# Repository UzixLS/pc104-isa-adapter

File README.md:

## PC104-ISA-ADAPTER
PC104 to ISA 16 bit adapter

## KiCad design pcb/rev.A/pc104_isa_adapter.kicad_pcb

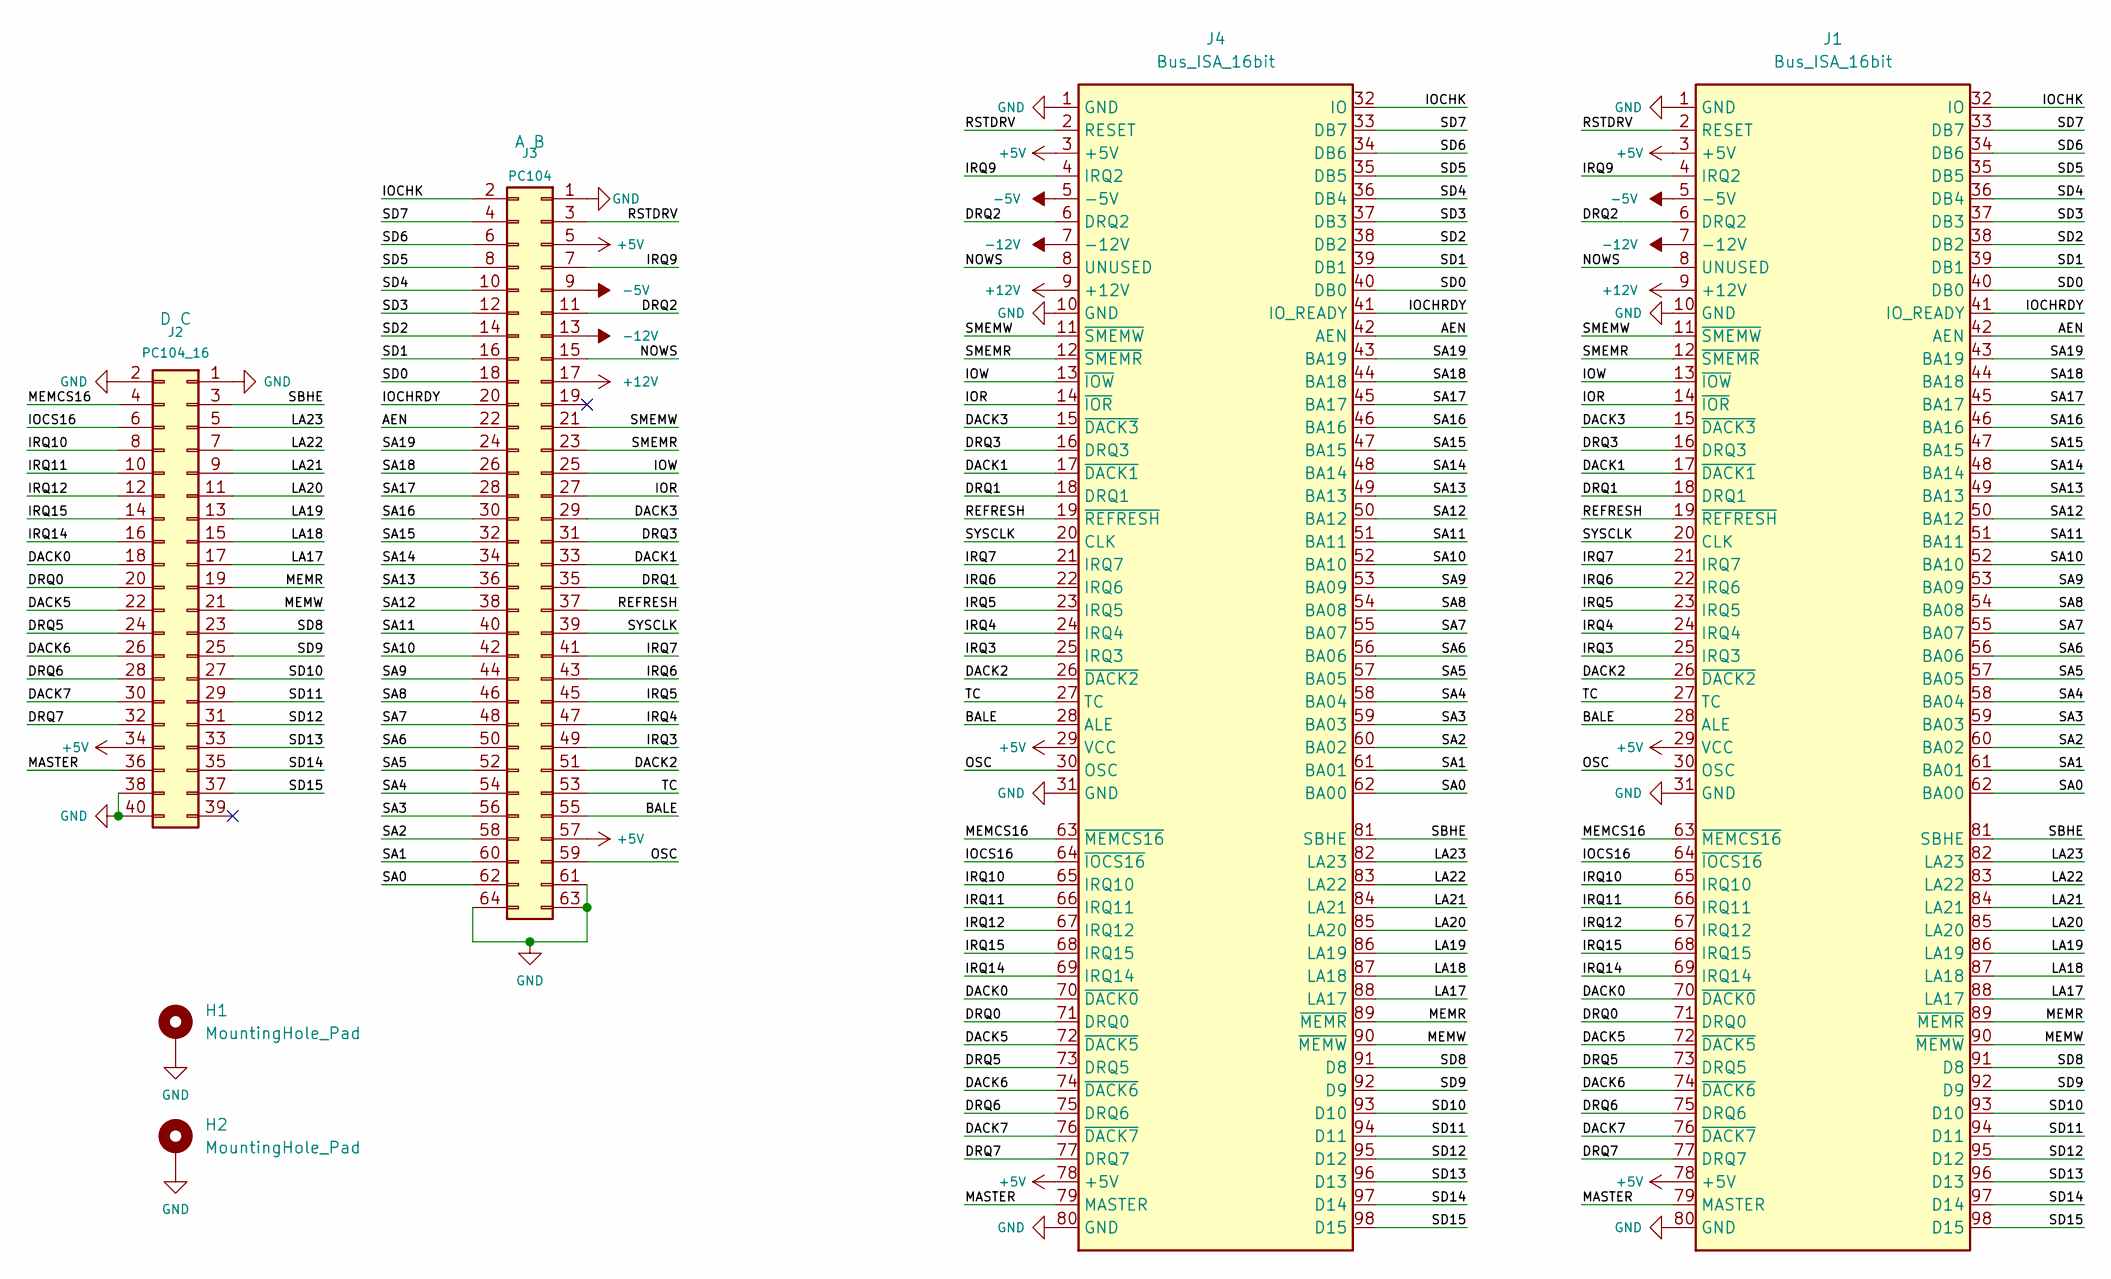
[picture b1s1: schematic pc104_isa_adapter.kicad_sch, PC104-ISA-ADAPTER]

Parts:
H1, H2: MountingHole_Pad; MountingHole_3.2mm_M3_Pad
J1: Bus_ISA_16bit; ISA16_EDGE
J2: PC104_16; PinSocket_2x20_P2.54mm_Vertical
J3: PC104; PinSocket_2x32_P2.54mm_Vertical
J4: Bus_ISA_16bit; ISA16

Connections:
+5V: J1.3 (+5V), J1.29 (VCC), J1.78 (+5V), J2.34, J3.5, J3.57, J4.3 (+5V), J4.29 (VCC), J4.78 (+5V)
+12V: J1.9 (+12V), J3.17, J4.9 (+12V)
-5V: J1.5 (-5V), J3.9, J4.5 (-5V)
-12V: J1.7 (-12V), J3.13, J4.7 (-12V)
/AEN: J1.42 (AEN), J3.22, J4.42 (AEN)
/BALE: J1.28 (ALE), J3.55, J4.28 (ALE)
/DACK0: J1.70 (~DACK0), J2.18, J4.70 (~DACK0)
/DACK1: J1.17 (~DACK1), J3.33, J4.17 (~DACK1)
/DACK2: J1.26 (~DACK2), J3.51, J4.26 (~DACK2)
/DACK3: J1.15 (~DACK3), J3.29, J4.15 (~DACK3)
/DACK5: J1.72 (~DACK5), J2.22, J4.72 (~DACK5)
/DACK6: J1.74 (~DACK6), J2.26, J4.74 (~DACK6)
/DACK7: J1.76 (~DACK7), J2.30, J4.76 (~DACK7)
/DRQ0: J1.71 (DRQ0), J2.20, J4.71 (DRQ0)
/DRQ1: J1.18 (DRQ1), J3.35, J4.18 (DRQ1)
/DRQ2: J1.6 (DRQ2), J3.11, J4.6 (DRQ2)
/DRQ3: J1.16 (DRQ3), J3.31, J4.16 (DRQ3)
/DRQ5: J1.73 (DRQ5), J2.24, J4.73 (DRQ5)
/DRQ6: J1.75 (DRQ6), J2.28, J4.75 (DRQ6)
/DRQ7: J1.77 (DRQ7), J2.32, J4.77 (DRQ7)
/IOCHK: J1.32 (IO), J3.2, J4.32 (IO)
/IOCHRDY: J1.41 (IO_READY), J3.20, J4.41 (IO_READY)
/IOCS16: J1.64 (~IOCS16), J2.6, J4.64 (~IOCS16)
/IOR: J1.14 (~IOR), J3.27, J4.14 (~IOR)
/IOW: J1.13 (~IOW), J3.25, J4.13 (~IOW)
/IRQ3: J1.25 (IRQ3), J3.49, J4.25 (IRQ3)
/IRQ4: J1.24 (IRQ4), J3.47, J4.24 (IRQ4)
/IRQ5: J1.23 (IRQ5), J3.45, J4.23 (IRQ5)
/IRQ6: J1.22 (IRQ6), J3.43, J4.22 (IRQ6)
/IRQ7: J1.21 (IRQ7), J3.41, J4.21 (IRQ7)
/IRQ9: J1.4 (IRQ2), J3.7, J4.4 (IRQ2)
/IRQ10: J1.65 (IRQ10), J2.8, J4.65 (IRQ10)
/IRQ11: J1.66 (IRQ11), J2.10, J4.66 (IRQ11)
/IRQ12: J1.67 (IRQ12), J2.12, J4.67 (IRQ12)
/IRQ14: J1.69 (IRQ14), J2.16, J4.69 (IRQ14)
/IRQ15: J1.68 (IRQ15), J2.14, J4.68 (IRQ15)
/LA17: J1.88 (LA17), J2.17, J4.88 (LA17)
/LA18: J1.87 (LA18), J2.15, J4.87 (LA18)
/LA19: J1.86 (LA19), J2.13, J4.86 (LA19)
/LA20: J1.85 (LA20), J2.11, J4.85 (LA20)
/LA21: J1.84 (LA21), J2.9, J4.84 (LA21)
/LA22: J1.83 (LA22), J2.7, J4.83 (LA22)
/LA23: J1.82 (LA23), J2.5, J4.82 (LA23)
/MASTER: J1.79 (MASTER), J2.36, J4.79 (MASTER)
/MEMCS16: J1.63 (~MEMCS16), J2.4, J4.63 (~MEMCS16)
/MEMR: J1.89 (~MEMR), J2.19, J4.89 (~MEMR)
/MEMW: J1.90 (~MEMW), J2.21, J4.90 (~MEMW)
/NOWS: J1.8 (UNUSED), J3.15, J4.8 (UNUSED)
/OSC: J1.30 (OSC), J3.59, J4.30 (OSC)
/REFRESH: J1.19 (~REFRESH), J3.37, J4.19 (~REFRESH)
/RSTDRV: J1.2 (RESET), J3.3, J4.2 (RESET)
/SA0: J1.62 (BA00), J3.62, J4.62 (BA00)
/SA1: J1.61 (BA01), J3.60, J4.61 (BA01)
/SA2: J1.60 (BA02), J3.58, J4.60 (BA02)
/SA3: J1.59 (BA03), J3.56, J4.59 (BA03)
/SA4: J1.58 (BA04), J3.54, J4.58 (BA04)
/SA5: J1.57 (BA05), J3.52, J4.57 (BA05)
/SA6: J1.56 (BA06), J3.50, J4.56 (BA06)
/SA7: J1.55 (BA07), J3.48, J4.55 (BA07)
/SA8: J1.54 (BA08), J3.46, J4.54 (BA08)
/SA9: J1.53 (BA09), J3.44, J4.53 (BA09)
/SA10: J1.52 (BA10), J3.42, J4.52 (BA10)
/SA11: J1.51 (BA11), J3.40, J4.51 (BA11)
/SA12: J1.50 (BA12), J3.38, J4.50 (BA12)
/SA13: J1.49 (BA13), J3.36, J4.49 (BA13)
/SA14: J1.48 (BA14), J3.34, J4.48 (BA14)
/SA15: J1.47 (BA15), J3.32, J4.47 (BA15)
/SA16: J1.46 (BA16), J3.30, J4.46 (BA16)
/SA17: J1.45 (BA17), J3.28, J4.45 (BA17)
/SA18: J1.44 (BA18), J3.26, J4.44 (BA18)
/SA19: J1.43 (BA19), J3.24, J4.43 (BA19)
/SBHE: J1.81 (SBHE), J2.3, J4.81 (SBHE)
/SD0: J1.40 (DB0), J3.18, J4.40 (DB0)
/SD1: J1.39 (DB1), J3.16, J4.39 (DB1)
/SD2: J1.38 (DB2), J3.14, J4.38 (DB2)
/SD3: J1.37 (DB3), J3.12, J4.37 (DB3)
/SD4: J1.36 (DB4), J3.10, J4.36 (DB4)
/SD5: J1.35 (DB5), J3.8, J4.35 (DB5)
/SD6: J1.34 (DB6), J3.6, J4.34 (DB6)
/SD7: J1.33 (DB7), J3.4, J4.33 (DB7)
/SD8: J1.91 (D8), J2.23, J4.91 (D8)
/SD9: J1.92 (D9), J2.25, J4.92 (D9)
/SD10: J1.93 (D10), J2.27, J4.93 (D10)
/SD11: J1.94 (D11), J2.29, J4.94 (D11)
/SD12: J1.95 (D12), J2.31, J4.95 (D12)
/SD13: J1.96 (D13), J2.33, J4.96 (D13)
/SD14: J1.97 (D14), J2.35, J4.97 (D14)
/SD15: J1.98 (D15), J2.37, J4.98 (D15)
/SMEMR: J1.12 (~SMEMR), J3.23, J4.12 (~SMEMR)
/SMEMW: J1.11 (~SMEMW), J3.21, J4.11 (~SMEMW)
/SYSCLK: J1.20 (CLK), J3.39, J4.20 (CLK)
/TC: J1.27 (TC), J3.53, J4.27 (TC)
GND: H1.1, H2.1, J1.1 (GND), J1.10 (GND), J1.31 (GND), J1.80 (GND), J2.1, J2.2, J2.38, J2.40, J3.1, J3.61, J3.63, J3.64, J4.1 (GND), J4.10 (GND), J4.31 (GND), J4.80 (GND)

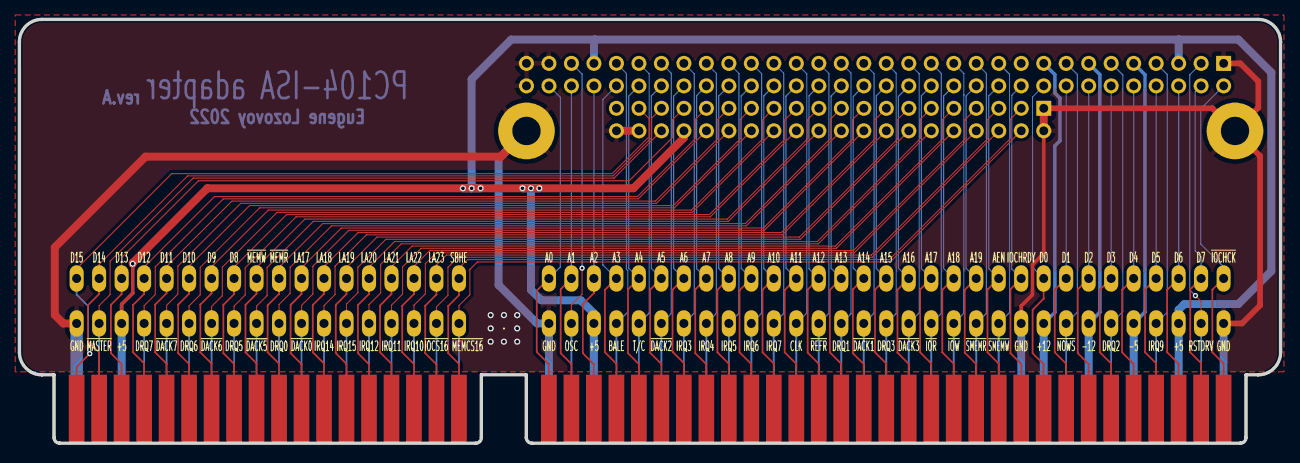
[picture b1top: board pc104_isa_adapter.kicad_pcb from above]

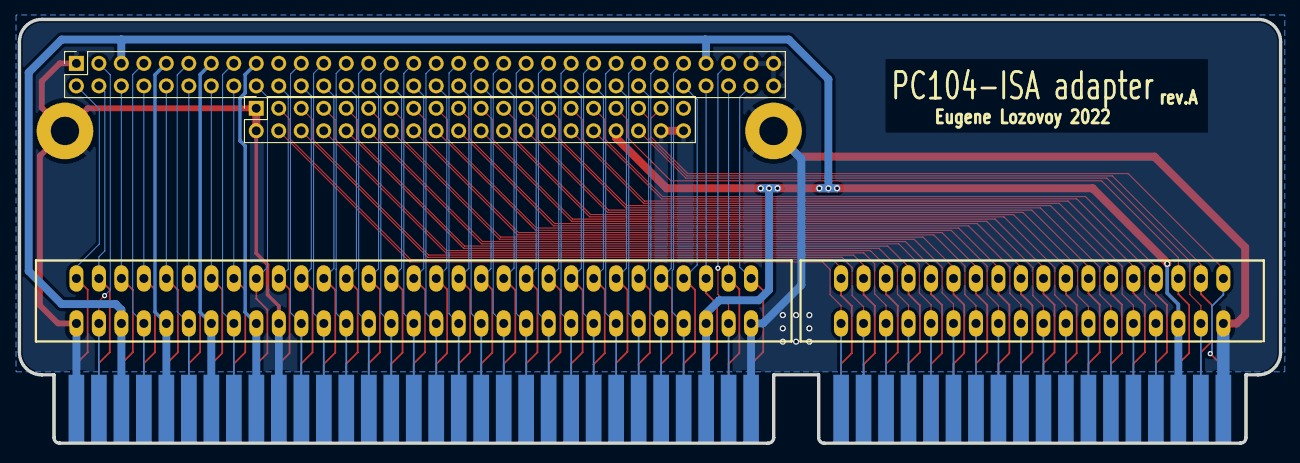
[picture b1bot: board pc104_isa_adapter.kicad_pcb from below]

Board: 2 copper layers, 142.4 x 47.9 mm, 6 parts (3 on the bottom side), 93 nets.

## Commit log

2022-09-14 add .gitignore and .gitattributes
2022-09-14 add pcb rev.A
2023-11-20 update pcb rev.A (final)
2023-11-20 release pcb rev.A
2023-11-25 add readme
